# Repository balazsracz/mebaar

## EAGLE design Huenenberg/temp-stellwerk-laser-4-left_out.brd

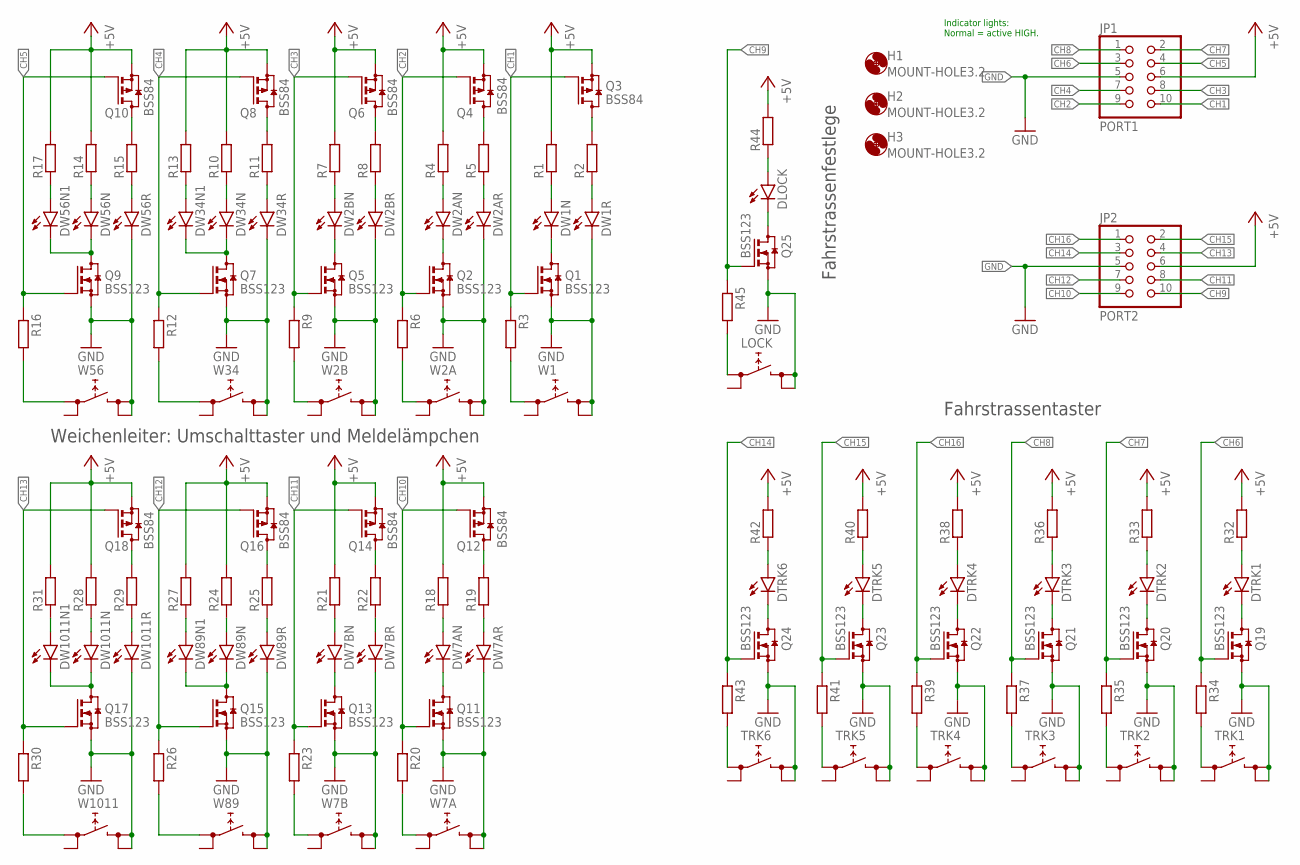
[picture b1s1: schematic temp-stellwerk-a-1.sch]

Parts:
DLOCK: LEDCHIP-LED0805; CHIP-LED0805
DTRK1, DTRK2, DTRK3, DTRK4, DTRK5, DTRK6: LEDCHIP-LED0805; CHIP-LED0805
DW1N, DW1R, DW2AN, DW2AR, DW7AR: LEDCHIP-LED0603; CHIP-LED0603
DW2BN, DW2BR, DW7BN, DW7BR, DW34N, DW34N1, DW34R, DW56N, DW56N1, DW56R, DW89N, DW89N1, DW89R, DW1011N, DW1011N1, DW1011R: LEDCHIP-LED0805; CHIP-LED0805
DW7AN: LEDCHIPLED_0603; CHIPLED_0603
H1, H2, H3: MOUNT-HOLE3.2; 3,2
JP1: PORT1; CON10M
JP2: PORT2; CON10M
LOCK: LOCK; TACTSW-6X6
Q1, Q2, Q5, Q7, Q9, Q11, Q13, Q15, Q17, Q19, Q20, Q21, Q22, Q23, Q24, Q25: BSS123; SOT23
Q3, Q4, Q6, Q8, Q10, Q12, Q14, Q16, Q18: BSS84; SOT23
R1, R2, R3, R4, R5, R6, R7, R8, R9, R10, R11, R12, R13, R14, R15, R16, R17, R18, R19, R20, R21, R22, R23, R24, R25, R26, R27, R28, R29, R30, R31, R32, R33, R34, R35, R36, R37, R38, R39, R40, R41, R42, R43, R44, R45: R-EU_R0805; R0805
TRK1, TRK2, TRK3, TRK4, TRK5, TRK6: TACTSW-6X6S; TACTSW-6X6
W1: W1; TACTSW-6X6
W2A, W2B, W7A, W7B: TACTSW-6X6S; TACTSW-6X6
W34, W56, W89, W1011: XOVER; TACTSW-6X6

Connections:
+5V: JP1.6, JP2.6, Q3.2 (S), Q4.2 (S), Q6.2 (S), Q8.2 (S), Q10.2 (S), Q12.2 (S), Q14.2 (S), Q16.2 (S), Q18.2 (S), R1.2, R4.2, R7.2, R10.2, R13.2, R14.2, R17.2, R18.2, R21.2, R24.2, R27.2, R28.2, R31.2, R32.2, R33.2, R36.2, R38.2, R40.2, R42.2, R44.2
CH1: JP1.10, Q1.1 (G), Q3.1 (G), R3.1
CH2: JP1.9, Q2.1 (G), Q4.1 (G), R6.1
CH3: JP1.8, Q5.1 (G), Q6.1 (G), R9.1
CH4: JP1.7, Q7.1 (G), Q8.1 (G), R12.1
CH5: JP1.4, Q9.1 (G), Q10.1 (G), R16.1
CH6: JP1.3, Q19.1 (G), R34.1
CH7: JP1.2, Q20.1 (G), R35.1
CH8: JP1.1, Q21.1 (G), R37.1
CH9: JP2.10, Q25.1 (G), R45.1
CH10: JP2.9, Q11.1 (G), Q12.1 (G), R20.1
CH11: JP2.8, Q13.1 (G), Q14.1 (G), R23.1
CH12: JP2.7, Q15.1 (G), Q16.1 (G), R26.1
CH13: JP2.4, Q17.1 (G), Q18.1 (G), R30.1
CH14: JP2.3, Q24.1 (G), R43.1
CH15: JP2.2, Q23.1 (G), R41.1
CH16: JP2.1, Q22.1 (G), R39.1
GND: DW1R.C, DW2AR.C, DW2BR.C, DW7AR.C, DW7BR.C, DW34R.C, DW56R.C, DW89R.C, DW1011R.C, JP1.5, JP2.5, LOCK.3 (2.1), LOCK.4 (2.2), Q1.2 (S), Q2.2 (S), Q5.2 (S), Q7.2 (S), Q9.2 (S), Q11.2 (S), Q13.2 (S), Q15.2 (S), Q17.2 (S), Q19.2 (S), Q20.2 (S), Q21.2 (S), Q22.2 (S), Q23.2 (S), Q24.2 (S), Q25.2 (S), TRK1.3 (2.1), TRK1.4 (2.2), TRK2.3 (2.1), TRK2.4 (2.2), TRK3.3 (2.1), TRK3.4 (2.2), TRK4.3 (2.1), TRK4.4 (2.2), TRK5.3 (2.1), TRK5.4 (2.2), TRK6.3 (2.1), TRK6.4 (2.2), W1.3 (2.1), W1.4 (2.2), W2A.3 (2.1), W2A.4 (2.2), W2B.3 (2.1), W2B.4 (2.2), W7A.3 (2.1), W7A.4 (2.2), W7B.3 (2.1), W7B.4 (2.2), W34.3 (2.1), W34.4 (2.2), W56.3 (2.1), W56.4 (2.2), W89.3 (2.1), W89.4 (2.2), W1011.3 (2.1), W1011.4 (2.2)
unnamed: DTRK1.C, Q19.3 (D)
unnamed: DW1N.C, Q1.3 (D)
unnamed: DW1N.A, R1.1
unnamed: DW1R.A, R2.1
unnamed: Q3.3 (D), R2.2
unnamed: DW2AN.C, Q2.3 (D)
unnamed: R3.2, W1.1 (1.1)
unnamed: DW2AN.A, R4.1
unnamed: DW2AR.A, R5.1
unnamed: Q4.3 (D), R5.2
unnamed: R6.2, W2A.1 (1.1)
unnamed: DW2BN.C, Q5.3 (D)
unnamed: DW2BN.A, R7.1
unnamed: DW2BR.A, R8.1
unnamed: Q6.3 (D), R8.2
unnamed: R9.2, W2B.1 (1.1)
unnamed: DW56N.A, R14.1
unnamed: DW34N.A, R10.1
unnamed: DW34R.A, R11.1
unnamed: Q8.3 (D), R11.2
unnamed: R12.2, W34.1 (1.1)
unnamed: DW34N.C, DW34N1.C, Q7.3 (D)
unnamed: DW34N1.A, R13.1
unnamed: DW56R.A, R15.1
unnamed: Q10.3 (D), R15.2
unnamed: R16.2, W56.1 (1.1)
unnamed: DW56N.C, DW56N1.C, Q9.3 (D)
unnamed: DW56N1.A, R17.1
unnamed: DW7AN.C, Q11.3 (D)
unnamed: DW7AN.A, R18.1
unnamed: DW7AR.A, R19.1
unnamed: Q12.3 (D), R19.2
unnamed: R20.2, W7A.1 (1.1)
unnamed: DW7BN.C, Q13.3 (D)
unnamed: DW7BN.A, R21.1
unnamed: DW7BR.A, R22.1
unnamed: Q14.3 (D), R22.2
unnamed: R23.2, W7B.1 (1.1)
unnamed: DW89N.A, R24.1
unnamed: DW89R.A, R25.1
unnamed: Q16.3 (D), R25.2
unnamed: R26.2, W89.1 (1.1)
unnamed: DW89N.C, DW89N1.C, Q15.3 (D)
unnamed: DW89N1.A, R27.1
unnamed: DW1011N.A, R28.1
unnamed: DW1011R.A, R29.1
unnamed: Q18.3 (D), R29.2
unnamed: R30.2, W1011.1 (1.1)
unnamed: DW1011N.C, DW1011N1.C, Q17.3 (D)
unnamed: DW1011N1.A, R31.1
unnamed: DTRK1.A, R32.1
unnamed: DTRK2.C, Q20.3 (D)
unnamed: DTRK2.A, R33.1
unnamed: R34.2, TRK1.1 (1.1)
unnamed: R35.2, TRK2.1 (1.1)
unnamed: DTRK3.C, Q21.3 (D)
unnamed: DTRK3.A, R36.1
unnamed: R37.2, TRK3.1 (1.1)
unnamed: DTRK4.C, Q22.3 (D)
unnamed: DTRK4.A, R38.1
unnamed: R39.2, TRK4.1 (1.1)
unnamed: DTRK5.C, Q23.3 (D)
unnamed: DTRK5.A, R40.1
unnamed: R41.2, TRK5.1 (1.1)
unnamed: DTRK6.C, Q24.3 (D)
unnamed: DTRK6.A, R42.1
unnamed: R43.2, TRK6.1 (1.1)
unnamed: DLOCK.C, Q25.3 (D)
unnamed: DLOCK.A, R44.1
unnamed: LOCK.1 (1.1), R45.2

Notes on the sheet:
Indicator lights: Normal = active HIGH.
Weichenleiter: Umschalttaster und Meldelämpchen
Fahrstrassentaster
Fahrstrassenfestlege

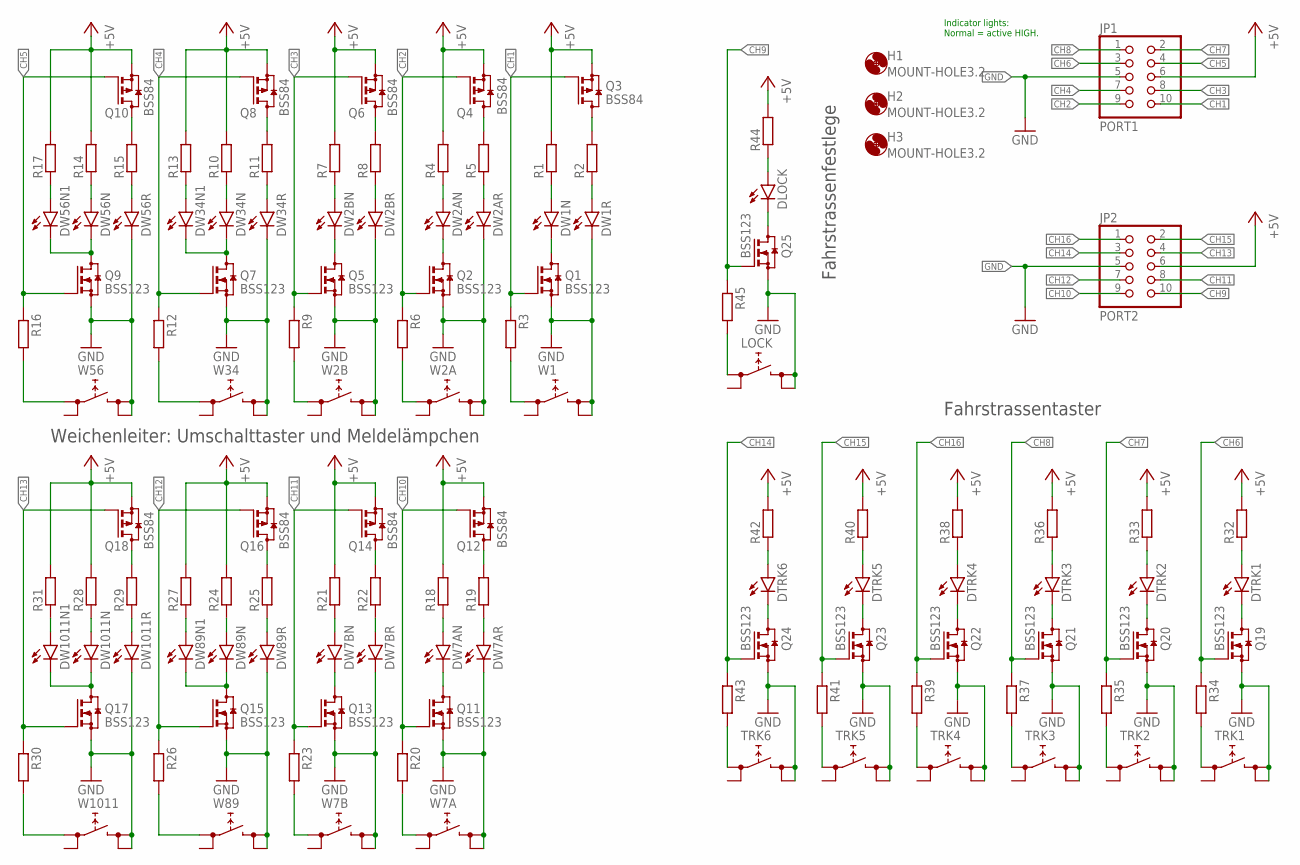
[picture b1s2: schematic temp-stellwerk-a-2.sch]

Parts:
DLOCK: LEDCHIP-LED0805; CHIP-LED0805
DTRK1, DTRK2, DTRK3, DTRK4, DTRK5, DTRK6: LEDCHIP-LED0805; CHIP-LED0805
DW1N, DW1R, DW2AN, DW2AR, DW7AR: LEDCHIP-LED0603; CHIP-LED0603
DW2BN, DW2BR, DW7BN, DW7BR, DW34N, DW34N1, DW34R, DW56N, DW56N1, DW56R, DW89N, DW89N1, DW89R, DW1011N, DW1011N1, DW1011R: LEDCHIP-LED0805; CHIP-LED0805
DW7AN: LEDCHIPLED_0603; CHIPLED_0603
H1, H2, H3: MOUNT-HOLE3.2; 3,2
JP1: PORT1; CON10M
JP2: PORT2; CON10M
LOCK: LOCK; TACTSW-6X6
Q1, Q2, Q5, Q7, Q9, Q11, Q13, Q15, Q17, Q19, Q20, Q21, Q22, Q23, Q24, Q25: BSS123; SOT23
Q3, Q4, Q6, Q8, Q10, Q12, Q14, Q16, Q18: BSS84; SOT23
R1, R2, R3, R4, R5, R6, R7, R8, R9, R10, R11, R12, R13, R14, R15, R16, R17, R18, R19, R20, R21, R22, R23, R24, R25, R26, R27, R28, R29, R30, R31, R32, R33, R34, R35, R36, R37, R38, R39, R40, R41, R42, R43, R44, R45: R-EU_R0805; R0805
TRK1, TRK2, TRK3, TRK4, TRK5, TRK6: TACTSW-6X6S; TACTSW-6X6
W1: W1; TACTSW-6X6
W2A, W2B, W7A, W7B: TACTSW-6X6S; TACTSW-6X6
W34, W56, W89, W1011: XOVER; TACTSW-6X6

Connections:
+5V: JP1.6, JP2.6, Q3.2 (S), Q4.2 (S), Q6.2 (S), Q8.2 (S), Q10.2 (S), Q12.2 (S), Q14.2 (S), Q16.2 (S), Q18.2 (S), R1.2, R4.2, R7.2, R10.2, R13.2, R14.2, R17.2, R18.2, R21.2, R24.2, R27.2, R28.2, R31.2, R32.2, R33.2, R36.2, R38.2, R40.2, R42.2, R44.2
CH1: JP1.10, Q1.1 (G), Q3.1 (G), R3.1
CH2: JP1.9, Q2.1 (G), Q4.1 (G), R6.1
CH3: JP1.8, Q5.1 (G), Q6.1 (G), R9.1
CH4: JP1.7, Q7.1 (G), Q8.1 (G), R12.1
CH5: JP1.4, Q9.1 (G), Q10.1 (G), R16.1
CH6: JP1.3, Q19.1 (G), R34.1
CH7: JP1.2, Q20.1 (G), R35.1
CH8: JP1.1, Q21.1 (G), R37.1
CH9: JP2.10, Q25.1 (G), R45.1
CH10: JP2.9, Q11.1 (G), Q12.1 (G), R20.1
CH11: JP2.8, Q13.1 (G), Q14.1 (G), R23.1
CH12: JP2.7, Q15.1 (G), Q16.1 (G), R26.1
CH13: JP2.4, Q17.1 (G), Q18.1 (G), R30.1
CH14: JP2.3, Q24.1 (G), R43.1
CH15: JP2.2, Q23.1 (G), R41.1
CH16: JP2.1, Q22.1 (G), R39.1
GND: DW1R.C, DW2AR.C, DW2BR.C, DW7AR.C, DW7BR.C, DW34R.C, DW56R.C, DW89R.C, DW1011R.C, JP1.5, JP2.5, LOCK.3 (2.1), LOCK.4 (2.2), Q1.2 (S), Q2.2 (S), Q5.2 (S), Q7.2 (S), Q9.2 (S), Q11.2 (S), Q13.2 (S), Q15.2 (S), Q17.2 (S), Q19.2 (S), Q20.2 (S), Q21.2 (S), Q22.2 (S), Q23.2 (S), Q24.2 (S), Q25.2 (S), TRK1.3 (2.1), TRK1.4 (2.2), TRK2.3 (2.1), TRK2.4 (2.2), TRK3.3 (2.1), TRK3.4 (2.2), TRK4.3 (2.1), TRK4.4 (2.2), TRK5.3 (2.1), TRK5.4 (2.2), TRK6.3 (2.1), TRK6.4 (2.2), W1.3 (2.1), W1.4 (2.2), W2A.3 (2.1), W2A.4 (2.2), W2B.3 (2.1), W2B.4 (2.2), W7A.3 (2.1), W7A.4 (2.2), W7B.3 (2.1), W7B.4 (2.2), W34.3 (2.1), W34.4 (2.2), W56.3 (2.1), W56.4 (2.2), W89.3 (2.1), W89.4 (2.2), W1011.3 (2.1), W1011.4 (2.2)
unnamed: DTRK1.C, Q19.3 (D)
unnamed: DW1N.C, Q1.3 (D)
unnamed: DW1N.A, R1.1
unnamed: DW1R.A, R2.1
unnamed: Q3.3 (D), R2.2
unnamed: DW2AN.C, Q2.3 (D)
unnamed: R3.2, W1.1 (1.1)
unnamed: DW2AN.A, R4.1
unnamed: DW2AR.A, R5.1
unnamed: Q4.3 (D), R5.2
unnamed: R6.2, W2A.1 (1.1)
unnamed: DW2BN.C, Q5.3 (D)
unnamed: DW2BN.A, R7.1
unnamed: DW2BR.A, R8.1
unnamed: Q6.3 (D), R8.2
unnamed: R9.2, W2B.1 (1.1)
unnamed: DW56N.A, R14.1
unnamed: DW34N.A, R10.1
unnamed: DW34R.A, R11.1
unnamed: Q8.3 (D), R11.2
unnamed: R12.2, W34.1 (1.1)
unnamed: DW34N.C, DW34N1.C, Q7.3 (D)
unnamed: DW34N1.A, R13.1
unnamed: DW56R.A, R15.1
unnamed: Q10.3 (D), R15.2
unnamed: R16.2, W56.1 (1.1)
unnamed: DW56N.C, DW56N1.C, Q9.3 (D)
unnamed: DW56N1.A, R17.1
unnamed: DW7AN.C, Q11.3 (D)
unnamed: DW7AN.A, R18.1
unnamed: DW7AR.A, R19.1
unnamed: Q12.3 (D), R19.2
unnamed: R20.2, W7A.1 (1.1)
unnamed: DW7BN.C, Q13.3 (D)
unnamed: DW7BN.A, R21.1
unnamed: DW7BR.A, R22.1
unnamed: Q14.3 (D), R22.2
unnamed: R23.2, W7B.1 (1.1)
unnamed: DW89N.A, R24.1
unnamed: DW89R.A, R25.1
unnamed: Q16.3 (D), R25.2
unnamed: R26.2, W89.1 (1.1)
unnamed: DW89N.C, DW89N1.C, Q15.3 (D)
unnamed: DW89N1.A, R27.1
unnamed: DW1011N.A, R28.1
unnamed: DW1011R.A, R29.1
unnamed: Q18.3 (D), R29.2
unnamed: R30.2, W1011.1 (1.1)
unnamed: DW1011N.C, DW1011N1.C, Q17.3 (D)
unnamed: DW1011N1.A, R31.1
unnamed: DTRK1.A, R32.1
unnamed: DTRK2.C, Q20.3 (D)
unnamed: DTRK2.A, R33.1
unnamed: R34.2, TRK1.1 (1.1)
unnamed: R35.2, TRK2.1 (1.1)
unnamed: DTRK3.C, Q21.3 (D)
unnamed: DTRK3.A, R36.1
unnamed: R37.2, TRK3.1 (1.1)
unnamed: DTRK4.C, Q22.3 (D)
unnamed: DTRK4.A, R38.1
unnamed: R39.2, TRK4.1 (1.1)
unnamed: DTRK5.C, Q23.3 (D)
unnamed: DTRK5.A, R40.1
unnamed: R41.2, TRK5.1 (1.1)
unnamed: DTRK6.C, Q24.3 (D)
unnamed: DTRK6.A, R42.1
unnamed: R43.2, TRK6.1 (1.1)
unnamed: DLOCK.C, Q25.3 (D)
unnamed: DLOCK.A, R44.1
unnamed: LOCK.1 (1.1), R45.2

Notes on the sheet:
Indicator lights: Normal = active HIGH.
Weichenleiter: Umschalttaster und Meldelämpchen
Fahrstrassentaster
Fahrstrassenfestlege

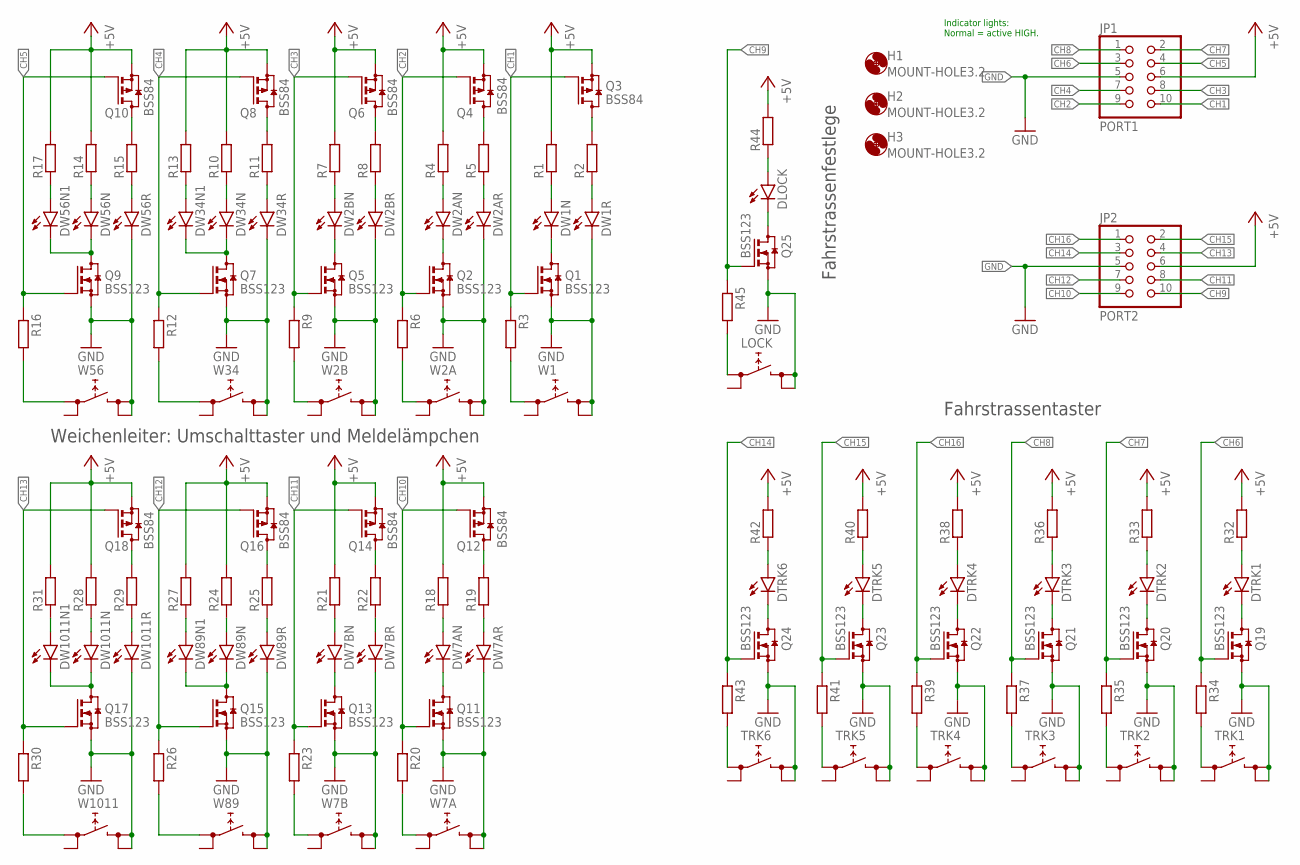
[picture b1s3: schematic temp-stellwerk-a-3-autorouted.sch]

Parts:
DLOCK: LEDCHIP-LED0805; CHIP-LED0805
DTRK1, DTRK2, DTRK3, DTRK4, DTRK5, DTRK6: LEDCHIP-LED0805; CHIP-LED0805
DW1N, DW1R, DW2AN, DW2AR, DW7AR: LEDCHIP-LED0603; CHIP-LED0603
DW2BN, DW2BR, DW7BN, DW7BR, DW34N, DW34N1, DW34R, DW56N, DW56N1, DW56R, DW89N, DW89N1, DW89R, DW1011N, DW1011N1, DW1011R: LEDCHIP-LED0805; CHIP-LED0805
DW7AN: LEDCHIPLED_0603; CHIPLED_0603
H1, H2, H3: MOUNT-HOLE3.2; 3,2
JP1: PORT1; CON10M
JP2: PORT2; CON10M
LOCK: LOCK; TACTSW-6X6
Q1, Q2, Q5, Q7, Q9, Q11, Q13, Q15, Q17, Q19, Q20, Q21, Q22, Q23, Q24, Q25: BSS123; SOT23-NCH
Q3, Q4, Q6, Q8, Q10, Q12, Q14, Q16, Q18: BSS84; SOT23
R1, R2, R3, R4, R5, R6, R7, R8, R9, R10, R11, R12, R13, R14, R15, R16, R17, R18, R19, R20, R21, R22, R23, R24, R25, R26, R27, R28, R29, R30, R31, R32, R33, R34, R35, R36, R37, R38, R39, R40, R41, R42, R43, R44, R45: R-EU_R0805; R0805
TRK1, TRK2, TRK3, TRK4, TRK5, TRK6: TACTSW-6X6S; TACTSW-6X6
W1: W1; TACTSW-6X6
W2A, W2B, W7A, W7B: TACTSW-6X6S; TACTSW-6X6
W34, W56, W89, W1011: XOVER; TACTSW-6X6

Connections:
+5V: JP1.6, JP2.6, Q3.2 (S), Q4.2 (S), Q6.2 (S), Q8.2 (S), Q10.2 (S), Q12.2 (S), Q14.2 (S), Q16.2 (S), Q18.2 (S), R1.2, R4.2, R7.2, R10.2, R13.2, R14.2, R17.2, R18.2, R21.2, R24.2, R27.2, R28.2, R31.2, R32.2, R33.2, R36.2, R38.2, R40.2, R42.2, R44.2
CH1: JP1.10, Q1.1 (G), Q3.1 (G), R3.1
CH2: JP1.9, Q2.1 (G), Q4.1 (G), R6.1
CH3: JP1.8, Q5.1 (G), Q6.1 (G), R9.1
CH4: JP1.7, Q7.1 (G), Q8.1 (G), R12.1
CH5: JP1.4, Q9.1 (G), Q10.1 (G), R16.1
CH6: JP1.3, Q19.1 (G), R34.1
CH7: JP1.2, Q20.1 (G), R35.1
CH8: JP1.1, Q21.1 (G), R37.1
CH9: JP2.10, Q25.1 (G), R45.1
CH10: JP2.9, Q11.1 (G), Q12.1 (G), R20.1
CH11: JP2.8, Q13.1 (G), Q14.1 (G), R23.1
CH12: JP2.7, Q15.1 (G), Q16.1 (G), R26.1
CH13: JP2.4, Q17.1 (G), Q18.1 (G), R30.1
CH14: JP2.3, Q24.1 (G), R43.1
CH15: JP2.2, Q23.1 (G), R41.1
CH16: JP2.1, Q22.1 (G), R39.1
GND: DW1R.C, DW2AR.C, DW2BR.C, DW7AR.C, DW7BR.C, DW34R.C, DW56R.C, DW89R.C, DW1011R.C, JP1.5, JP2.5, LOCK.3 (2.1), LOCK.4 (2.2), Q1.2 (S), Q2.2 (S), Q5.2 (S), Q7.2 (S), Q9.2 (S), Q11.2 (S), Q13.2 (S), Q15.2 (S), Q17.2 (S), Q19.2 (S), Q20.2 (S), Q21.2 (S), Q22.2 (S), Q23.2 (S), Q24.2 (S), Q25.2 (S), TRK1.3 (2.1), TRK1.4 (2.2), TRK2.3 (2.1), TRK2.4 (2.2), TRK3.3 (2.1), TRK3.4 (2.2), TRK4.3 (2.1), TRK4.4 (2.2), TRK5.3 (2.1), TRK5.4 (2.2), TRK6.3 (2.1), TRK6.4 (2.2), W1.3 (2.1), W1.4 (2.2), W2A.3 (2.1), W2A.4 (2.2), W2B.3 (2.1), W2B.4 (2.2), W7A.3 (2.1), W7A.4 (2.2), W7B.3 (2.1), W7B.4 (2.2), W34.3 (2.1), W34.4 (2.2), W56.3 (2.1), W56.4 (2.2), W89.3 (2.1), W89.4 (2.2), W1011.3 (2.1), W1011.4 (2.2)
unnamed: DTRK1.C, Q19.3 (D)
unnamed: DW1N.C, Q1.3 (D)
unnamed: DW1N.A, R1.1
unnamed: DW1R.A, R2.1
unnamed: Q3.3 (D), R2.2
unnamed: DW2AN.C, Q2.3 (D)
unnamed: R3.2, W1.1 (1.1)
unnamed: DW2AN.A, R4.1
unnamed: DW2AR.A, R5.1
unnamed: Q4.3 (D), R5.2
unnamed: R6.2, W2A.1 (1.1)
unnamed: DW2BN.C, Q5.3 (D)
unnamed: DW2BN.A, R7.1
unnamed: DW2BR.A, R8.1
unnamed: Q6.3 (D), R8.2
unnamed: R9.2, W2B.1 (1.1)
unnamed: DW56N.A, R14.1
unnamed: DW34N.A, R10.1
unnamed: DW34R.A, R11.1
unnamed: Q8.3 (D), R11.2
unnamed: R12.2, W34.1 (1.1)
unnamed: DW34N.C, DW34N1.C, Q7.3 (D)
unnamed: DW34N1.A, R13.1
unnamed: DW56R.A, R15.1
unnamed: Q10.3 (D), R15.2
unnamed: R16.2, W56.1 (1.1)
unnamed: DW56N.C, DW56N1.C, Q9.3 (D)
unnamed: DW56N1.A, R17.1
unnamed: DW7AN.C, Q11.3 (D)
unnamed: DW7AN.A, R18.1
unnamed: DW7AR.A, R19.1
unnamed: Q12.3 (D), R19.2
unnamed: R20.2, W7A.1 (1.1)
unnamed: DW7BN.C, Q13.3 (D)
unnamed: DW7BN.A, R21.1
unnamed: DW7BR.A, R22.1
unnamed: Q14.3 (D), R22.2
unnamed: R23.2, W7B.1 (1.1)
unnamed: DW89N.A, R24.1
unnamed: DW89R.A, R25.1
unnamed: Q16.3 (D), R25.2
unnamed: R26.2, W89.1 (1.1)
unnamed: DW89N.C, DW89N1.C, Q15.3 (D)
unnamed: DW89N1.A, R27.1
unnamed: DW1011N.A, R28.1
unnamed: DW1011R.A, R29.1
unnamed: Q18.3 (D), R29.2
unnamed: R30.2, W1011.1 (1.1)
unnamed: DW1011N.C, DW1011N1.C, Q17.3 (D)
unnamed: DW1011N1.A, R31.1
unnamed: DTRK1.A, R32.1
unnamed: DTRK2.C, Q20.3 (D)
unnamed: DTRK2.A, R33.1
unnamed: R34.2, TRK1.1 (1.1)
unnamed: R35.2, TRK2.1 (1.1)
unnamed: DTRK3.C, Q21.3 (D)
unnamed: DTRK3.A, R36.1
unnamed: R37.2, TRK3.1 (1.1)
unnamed: DTRK4.C, Q22.3 (D)
unnamed: DTRK4.A, R38.1
unnamed: R39.2, TRK4.1 (1.1)
unnamed: DTRK5.C, Q23.3 (D)
unnamed: DTRK5.A, R40.1
unnamed: R41.2, TRK5.1 (1.1)
unnamed: DTRK6.C, Q24.3 (D)
unnamed: DTRK6.A, R42.1
unnamed: R43.2, TRK6.1 (1.1)
unnamed: DLOCK.C, Q25.3 (D)
unnamed: DLOCK.A, R44.1
unnamed: LOCK.1 (1.1), R45.2

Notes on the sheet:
Indicator lights: Normal = active HIGH.
Weichenleiter: Umschalttaster und Meldelämpchen
Fahrstrassentaster
Fahrstrassenfestlege

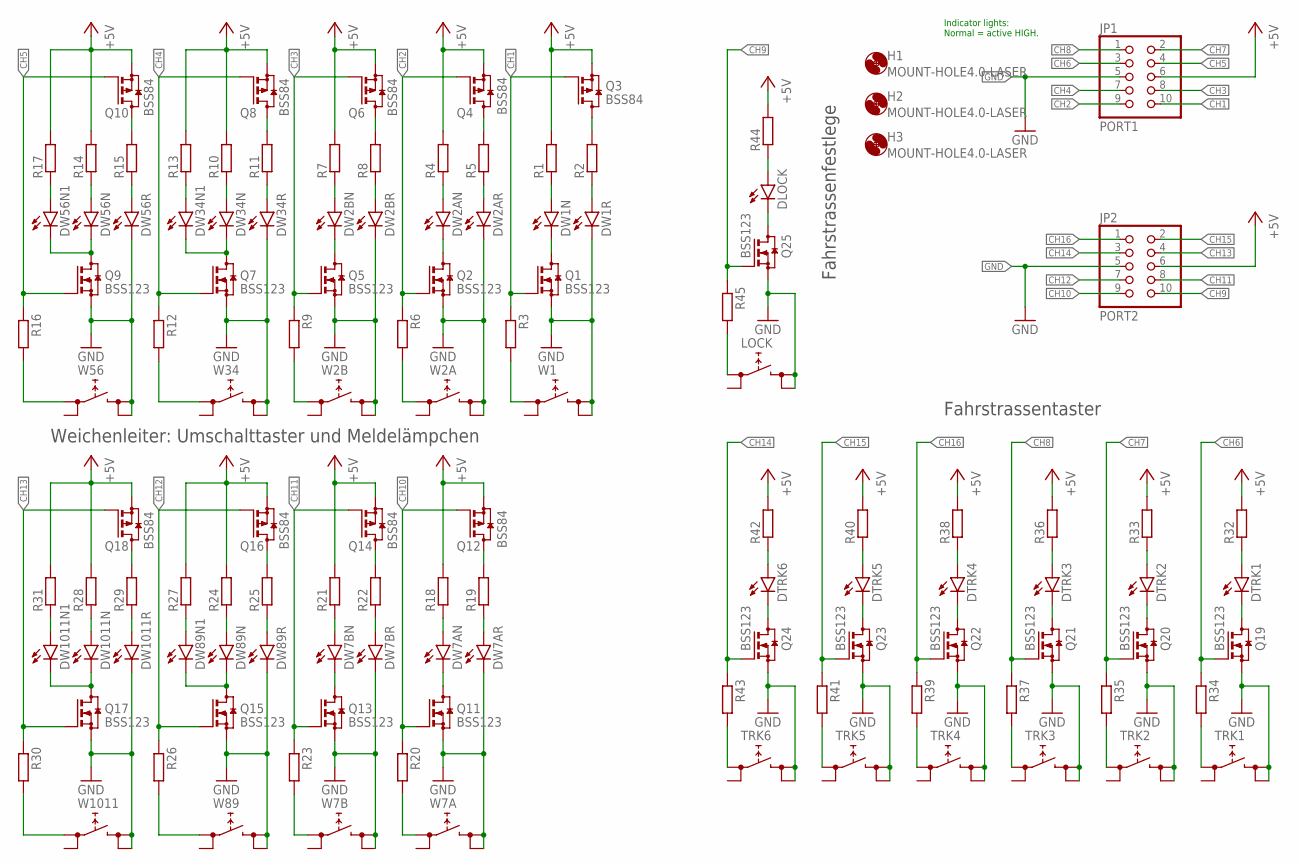
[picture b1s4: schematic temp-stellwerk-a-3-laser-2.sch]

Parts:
DLOCK: LEDCHIPLED_0805; CHIPLED_0805
DTRK1, DTRK2, DTRK3, DTRK4, DTRK5, DTRK6: LEDCHIPLED_0805; CHIPLED_0805
DW1N, DW1R, DW2AN, DW2AR, DW7AN, DW7AR: LEDCHIPLED_0603; CHIPLED_0603
DW2BN, DW2BR, DW7BN, DW7BR, DW34N, DW34N1, DW34R, DW56N, DW56N1, DW56R, DW89N, DW89N1, DW89R, DW1011N, DW1011N1, DW1011R: LEDCHIPLED_0805; CHIPLED_0805
H1, H2, H3: MOUNT-HOLE4.0-LASER; MOUNT-HOLE-3.2-4.0-LASER
JP1: PORT1; CON10M
JP2: PORT2; CON10M
LOCK: LOCK; TACTSW-6X6-LASER
Q1, Q2, Q5, Q7, Q9, Q11, Q13, Q15, Q17, Q19, Q20, Q21, Q22, Q23, Q24, Q25: BSS123; SOT23-NCH
Q3, Q4, Q6, Q8, Q10, Q12, Q14, Q16, Q18: BSS84; SOT23
R1, R2, R3, R4, R5, R6, R7, R8, R9, R10, R11, R12, R13, R14, R15, R16, R17, R18, R19, R20, R21, R22, R23, R24, R25, R26, R27, R28, R29, R30, R31, R32, R33, R34, R35, R36, R37, R38, R39, R40, R41, R42, R43, R44, R45: R-EU_R0805; R0805
TRK1, TRK2, TRK3, TRK4, TRK5, TRK6: TACTSW-6X6S; TACTSW-6X6-LASER
W1: W1; TACTSW-6X6-LASER
W2A, W2B, W7A, W7B: TACTSW-6X6S; TACTSW-6X6-LASER
W34, W56, W89, W1011: XOVER; TACTSW-6X6-LASER

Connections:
+5V: JP1.6, JP2.6, Q3.2 (S), Q4.2 (S), Q6.2 (S), Q8.2 (S), Q10.2 (S), Q12.2 (S), Q14.2 (S), Q16.2 (S), Q18.2 (S), R1.2, R4.2, R7.2, R10.2, R13.2, R14.2, R17.2, R18.2, R21.2, R24.2, R27.2, R28.2, R31.2, R32.2, R33.2, R36.2, R38.2, R40.2, R42.2, R44.2
CH1: JP1.10, Q1.1 (G), Q3.1 (G), R3.1
CH2: JP1.9, Q2.1 (G), Q4.1 (G), R6.1
CH3: JP1.8, Q5.1 (G), Q6.1 (G), R9.1
CH4: JP1.7, Q7.1 (G), Q8.1 (G), R12.1
CH5: JP1.4, Q9.1 (G), Q10.1 (G), R16.1
CH6: JP1.3, Q19.1 (G), R34.1
CH7: JP1.2, Q20.1 (G), R35.1
CH8: JP1.1, Q21.1 (G), R37.1
CH9: JP2.10, Q25.1 (G), R45.1
CH10: JP2.9, Q11.1 (G), Q12.1 (G), R20.1
CH11: JP2.8, Q13.1 (G), Q14.1 (G), R23.1
CH12: JP2.7, Q15.1 (G), Q16.1 (G), R26.1
CH13: JP2.4, Q17.1 (G), Q18.1 (G), R30.1
CH14: JP2.3, Q24.1 (G), R43.1
CH15: JP2.2, Q23.1 (G), R41.1
CH16: JP2.1, Q22.1 (G), R39.1
GND: DW1R.C, DW2AR.C, DW2BR.C, DW7AR.C, DW7BR.C, DW34R.C, DW56R.C, DW89R.C, DW1011R.C, JP1.5, JP2.5, LOCK.3 (2.1), LOCK.4 (2.2), Q1.2 (S), Q2.2 (S), Q5.2 (S), Q7.2 (S), Q9.2 (S), Q11.2 (S), Q13.2 (S), Q15.2 (S), Q17.2 (S), Q19.2 (S), Q20.2 (S), Q21.2 (S), Q22.2 (S), Q23.2 (S), Q24.2 (S), Q25.2 (S), TRK1.3 (2.1), TRK1.4 (2.2), TRK2.3 (2.1), TRK2.4 (2.2), TRK3.3 (2.1), TRK3.4 (2.2), TRK4.3 (2.1), TRK4.4 (2.2), TRK5.3 (2.1), TRK5.4 (2.2), TRK6.3 (2.1), TRK6.4 (2.2), W1.3 (2.1), W1.4 (2.2), W2A.3 (2.1), W2A.4 (2.2), W2B.3 (2.1), W2B.4 (2.2), W7A.3 (2.1), W7A.4 (2.2), W7B.3 (2.1), W7B.4 (2.2), W34.3 (2.1), W34.4 (2.2), W56.3 (2.1), W56.4 (2.2), W89.3 (2.1), W89.4 (2.2), W1011.3 (2.1), W1011.4 (2.2)
unnamed: DTRK1.C, Q19.3 (D)
unnamed: DW1N.C, Q1.3 (D)
unnamed: DW1N.A, R1.1
unnamed: DW1R.A, R2.1
unnamed: Q3.3 (D), R2.2
unnamed: DW2AN.C, Q2.3 (D)
unnamed: R3.2, W1.1 (1.1)
unnamed: DW2AN.A, R4.1
unnamed: DW2AR.A, R5.1
unnamed: Q4.3 (D), R5.2
unnamed: R6.2, W2A.1 (1.1)
unnamed: DW2BN.C, Q5.3 (D)
unnamed: DW2BN.A, R7.1
unnamed: DW2BR.A, R8.1
unnamed: Q6.3 (D), R8.2
unnamed: R9.2, W2B.1 (1.1)
unnamed: DW56N.A, R14.1
unnamed: DW34N.A, R10.1
unnamed: DW34R.A, R11.1
unnamed: Q8.3 (D), R11.2
unnamed: R12.2, W34.1 (1.1)
unnamed: DW34N.C, DW34N1.C, Q7.3 (D)
unnamed: DW34N1.A, R13.1
unnamed: DW56R.A, R15.1
unnamed: Q10.3 (D), R15.2
unnamed: R16.2, W56.1 (1.1)
unnamed: DW56N.C, DW56N1.C, Q9.3 (D)
unnamed: DW56N1.A, R17.1
unnamed: DW7AN.C, Q11.3 (D)
unnamed: DW7AN.A, R18.1
unnamed: DW7AR.A, R19.1
unnamed: Q12.3 (D), R19.2
unnamed: R20.2, W7A.1 (1.1)
unnamed: DW7BN.C, Q13.3 (D)
unnamed: DW7BN.A, R21.1
unnamed: DW7BR.A, R22.1
unnamed: Q14.3 (D), R22.2
unnamed: R23.2, W7B.1 (1.1)
unnamed: DW89N.A, R24.1
unnamed: DW89R.A, R25.1
unnamed: Q16.3 (D), R25.2
unnamed: R26.2, W89.1 (1.1)
unnamed: DW89N.C, DW89N1.C, Q15.3 (D)
unnamed: DW89N1.A, R27.1
unnamed: DW1011N.A, R28.1
unnamed: DW1011R.A, R29.1
unnamed: Q18.3 (D), R29.2
unnamed: R30.2, W1011.1 (1.1)
unnamed: DW1011N.C, DW1011N1.C, Q17.3 (D)
unnamed: DW1011N1.A, R31.1
unnamed: DTRK1.A, R32.1
unnamed: DTRK2.C, Q20.3 (D)
unnamed: DTRK2.A, R33.1
unnamed: R34.2, TRK1.1 (1.1)
unnamed: R35.2, TRK2.1 (1.1)
unnamed: DTRK3.C, Q21.3 (D)
unnamed: DTRK3.A, R36.1
unnamed: R37.2, TRK3.1 (1.1)
unnamed: DTRK4.C, Q22.3 (D)
unnamed: DTRK4.A, R38.1
unnamed: R39.2, TRK4.1 (1.1)
unnamed: DTRK5.C, Q23.3 (D)
unnamed: DTRK5.A, R40.1
unnamed: R41.2, TRK5.1 (1.1)
unnamed: DTRK6.C, Q24.3 (D)
unnamed: DTRK6.A, R42.1
unnamed: R43.2, TRK6.1 (1.1)
unnamed: DLOCK.C, Q25.3 (D)
unnamed: DLOCK.A, R44.1
unnamed: LOCK.1 (1.1), R45.2

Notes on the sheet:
Indicator lights: Normal = active HIGH.
Weichenleiter: Umschalttaster und Meldelämpchen
Fahrstrassentaster
Fahrstrassenfestlege

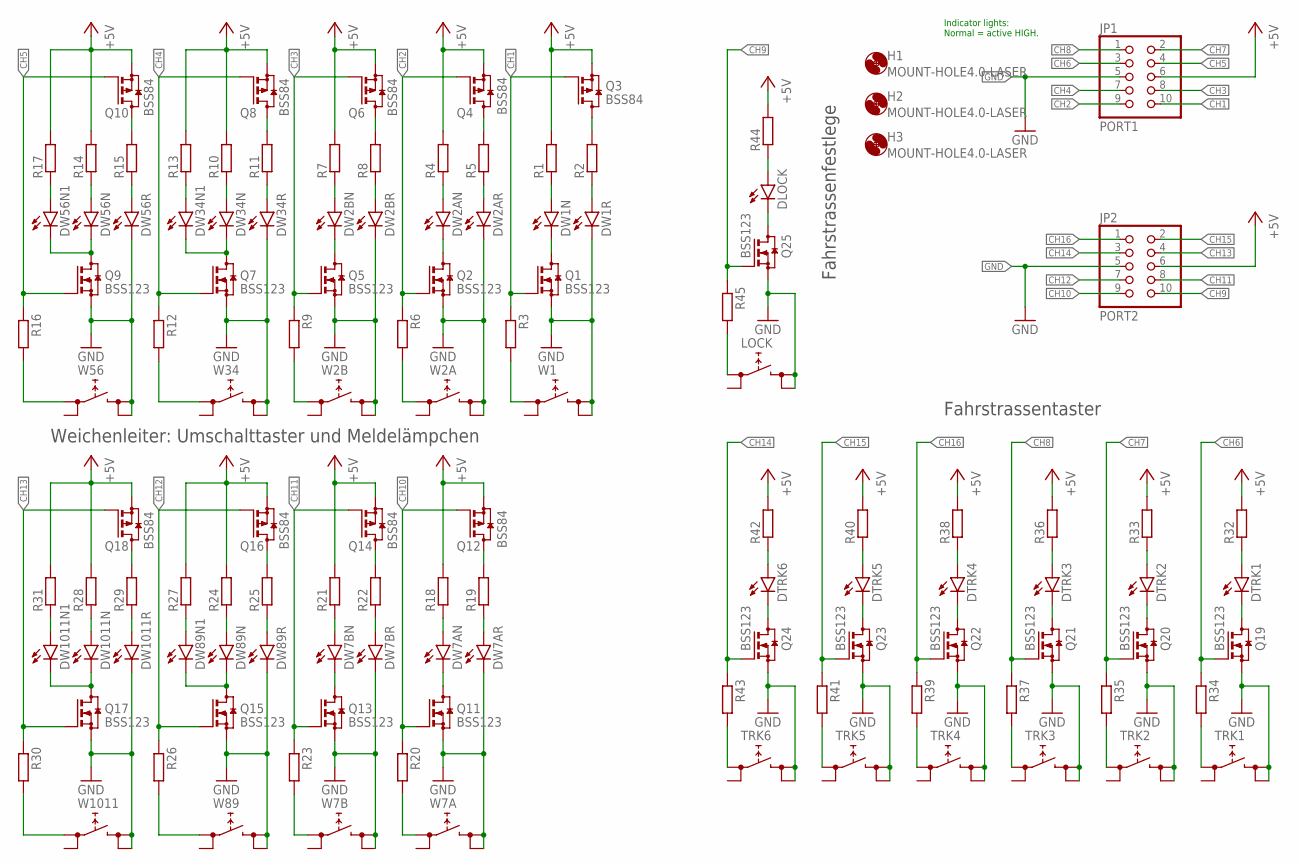
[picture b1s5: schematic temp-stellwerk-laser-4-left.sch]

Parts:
DLOCK: LEDCHIPLED_0805; CHIPLED_0805
DTRK1, DTRK2, DTRK3, DTRK4, DTRK5, DTRK6: LEDCHIPLED_0805; CHIPLED_0805
DW1N, DW1R, DW2AN, DW2AR, DW7AN, DW7AR: LEDCHIPLED_0603; CHIPLED_0603
DW2BN, DW2BR, DW7BN, DW7BR, DW34N, DW34N1, DW34R, DW56N, DW56N1, DW56R, DW89N, DW89N1, DW89R, DW1011N, DW1011N1, DW1011R: LEDCHIPLED_0805; CHIPLED_0805
H1, H2, H3: MOUNT-HOLE4.0-LASER; MOUNT-HOLE-3.2-4.0-LASER
JP1: PORT1; CON10M
JP2: PORT2; CON10M
LOCK: LOCK; TACTSW-6X6-LASER
Q1, Q2, Q5, Q7, Q9, Q11, Q13, Q15, Q17, Q19, Q20, Q21, Q22, Q23, Q24, Q25: BSS123; SOT23-NCH
Q3, Q4, Q6, Q8, Q10, Q12, Q14, Q16, Q18: BSS84; SOT23
R1, R2, R3, R4, R5, R6, R7, R8, R9, R10, R11, R12, R13, R14, R15, R16, R17, R18, R19, R20, R21, R22, R23, R24, R25, R26, R27, R28, R29, R30, R31, R32, R33, R34, R35, R36, R37, R38, R39, R40, R41, R42, R43, R44, R45: R-EU_R0805; R0805
TRK1, TRK2, TRK3, TRK4, TRK5, TRK6: TACTSW-6X6S; TACTSW-6X6-LASER
W1: W1; TACTSW-6X6-LASER
W2A, W2B, W7A, W7B: TACTSW-6X6S; TACTSW-6X6-LASER
W34, W56, W89, W1011: XOVER; TACTSW-6X6-LASER

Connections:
+5V: JP1.6, JP2.6, Q3.2 (S), Q4.2 (S), Q6.2 (S), Q8.2 (S), Q10.2 (S), Q12.2 (S), Q14.2 (S), Q16.2 (S), Q18.2 (S), R1.2, R4.2, R7.2, R10.2, R13.2, R14.2, R17.2, R18.2, R21.2, R24.2, R27.2, R28.2, R31.2, R32.2, R33.2, R36.2, R38.2, R40.2, R42.2, R44.2
CH1: JP1.10, Q1.1 (G), Q3.1 (G), R3.1
CH2: JP1.9, Q2.1 (G), Q4.1 (G), R6.1
CH3: JP1.8, Q5.1 (G), Q6.1 (G), R9.1
CH4: JP1.7, Q7.1 (G), Q8.1 (G), R12.1
CH5: JP1.4, Q9.1 (G), Q10.1 (G), R16.1
CH6: JP1.3, Q19.1 (G), R34.1
CH7: JP1.2, Q20.1 (G), R35.1
CH8: JP1.1, Q21.1 (G), R37.1
CH9: JP2.10, Q25.1 (G), R45.1
CH10: JP2.9, Q11.1 (G), Q12.1 (G), R20.1
CH11: JP2.8, Q13.1 (G), Q14.1 (G), R23.1
CH12: JP2.7, Q15.1 (G), Q16.1 (G), R26.1
CH13: JP2.4, Q17.1 (G), Q18.1 (G), R30.1
CH14: JP2.3, Q24.1 (G), R43.1
CH15: JP2.2, Q23.1 (G), R41.1
CH16: JP2.1, Q22.1 (G), R39.1
GND: DW1R.C, DW2AR.C, DW2BR.C, DW7AR.C, DW7BR.C, DW34R.C, DW56R.C, DW89R.C, DW1011R.C, JP1.5, JP2.5, LOCK.3 (2.1), LOCK.4 (2.2), Q1.2 (S), Q2.2 (S), Q5.2 (S), Q7.2 (S), Q9.2 (S), Q11.2 (S), Q13.2 (S), Q15.2 (S), Q17.2 (S), Q19.2 (S), Q20.2 (S), Q21.2 (S), Q22.2 (S), Q23.2 (S), Q24.2 (S), Q25.2 (S), TRK1.3 (2.1), TRK1.4 (2.2), TRK2.3 (2.1), TRK2.4 (2.2), TRK3.3 (2.1), TRK3.4 (2.2), TRK4.3 (2.1), TRK4.4 (2.2), TRK5.3 (2.1), TRK5.4 (2.2), TRK6.3 (2.1), TRK6.4 (2.2), W1.3 (2.1), W1.4 (2.2), W2A.3 (2.1), W2A.4 (2.2), W2B.3 (2.1), W2B.4 (2.2), W7A.3 (2.1), W7A.4 (2.2), W7B.3 (2.1), W7B.4 (2.2), W34.3 (2.1), W34.4 (2.2), W56.3 (2.1), W56.4 (2.2), W89.3 (2.1), W89.4 (2.2), W1011.3 (2.1), W1011.4 (2.2)
unnamed: DTRK1.C, Q19.3 (D)
unnamed: DW1N.C, Q1.3 (D)
unnamed: DW1N.A, R1.1
unnamed: DW1R.A, R2.1
unnamed: Q3.3 (D), R2.2
unnamed: DW2AN.C, Q2.3 (D)
unnamed: R3.2, W1.1 (1.1)
unnamed: DW2AN.A, R4.1
unnamed: DW2AR.A, R5.1
unnamed: Q4.3 (D), R5.2
unnamed: R6.2, W2A.1 (1.1)
unnamed: DW2BN.C, Q5.3 (D)
unnamed: DW2BN.A, R7.1
unnamed: DW2BR.A, R8.1
unnamed: Q6.3 (D), R8.2
unnamed: R9.2, W2B.1 (1.1)
unnamed: DW56N.A, R14.1
unnamed: DW34N.A, R10.1
unnamed: DW34R.A, R11.1
unnamed: Q8.3 (D), R11.2
unnamed: R12.2, W34.1 (1.1)
unnamed: DW34N.C, DW34N1.C, Q7.3 (D)
unnamed: DW34N1.A, R13.1
unnamed: DW56R.A, R15.1
unnamed: Q10.3 (D), R15.2
unnamed: R16.2, W56.1 (1.1)
unnamed: DW56N.C, DW56N1.C, Q9.3 (D)
unnamed: DW56N1.A, R17.1
unnamed: DW7AN.C, Q11.3 (D)
unnamed: DW7AN.A, R18.1
unnamed: DW7AR.A, R19.1
unnamed: Q12.3 (D), R19.2
unnamed: R20.2, W7A.1 (1.1)
unnamed: DW7BN.C, Q13.3 (D)
unnamed: DW7BN.A, R21.1
unnamed: DW7BR.A, R22.1
unnamed: Q14.3 (D), R22.2
unnamed: R23.2, W7B.1 (1.1)
unnamed: DW89N.A, R24.1
unnamed: DW89R.A, R25.1
unnamed: Q16.3 (D), R25.2
unnamed: R26.2, W89.1 (1.1)
unnamed: DW89N.C, DW89N1.C, Q15.3 (D)
unnamed: DW89N1.A, R27.1
unnamed: DW1011N.A, R28.1
unnamed: DW1011R.A, R29.1
unnamed: Q18.3 (D), R29.2
unnamed: R30.2, W1011.1 (1.1)
unnamed: DW1011N.C, DW1011N1.C, Q17.3 (D)
unnamed: DW1011N1.A, R31.1
unnamed: DTRK1.A, R32.1
unnamed: DTRK2.C, Q20.3 (D)
unnamed: DTRK2.A, R33.1
unnamed: R34.2, TRK1.1 (1.1)
unnamed: R35.2, TRK2.1 (1.1)
unnamed: DTRK3.C, Q21.3 (D)
unnamed: DTRK3.A, R36.1
unnamed: R37.2, TRK3.1 (1.1)
unnamed: DTRK4.C, Q22.3 (D)
unnamed: DTRK4.A, R38.1
unnamed: R39.2, TRK4.1 (1.1)
unnamed: DTRK5.C, Q23.3 (D)
unnamed: DTRK5.A, R40.1
unnamed: R41.2, TRK5.1 (1.1)
unnamed: DTRK6.C, Q24.3 (D)
unnamed: DTRK6.A, R42.1
unnamed: R43.2, TRK6.1 (1.1)
unnamed: DLOCK.C, Q25.3 (D)
unnamed: DLOCK.A, R44.1
unnamed: LOCK.1 (1.1), R45.2

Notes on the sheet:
Indicator lights: Normal = active HIGH.
Weichenleiter: Umschalttaster und Meldelämpchen
Fahrstrassentaster
Fahrstrassenfestlege

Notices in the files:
Schalterwerk/Gleisbelegung/gleis-a-1.sch:
LICENSE: Licensed by the Solderpad Hardware License V2.0
parts and their libraries:
COPYRIGHT: Copyright (C) 2023 Ultra Librarian. All rights reserved.
